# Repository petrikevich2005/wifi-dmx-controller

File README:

этот репозиторий предназначен для хранения прошивки микроконтроллера этого проекта: https://docs.google.com/document/d/1X2l_9bCAOKjv8QiKN7pxREiMzuwiFvaY4nnqX09m9t8/edit?usp=sharing

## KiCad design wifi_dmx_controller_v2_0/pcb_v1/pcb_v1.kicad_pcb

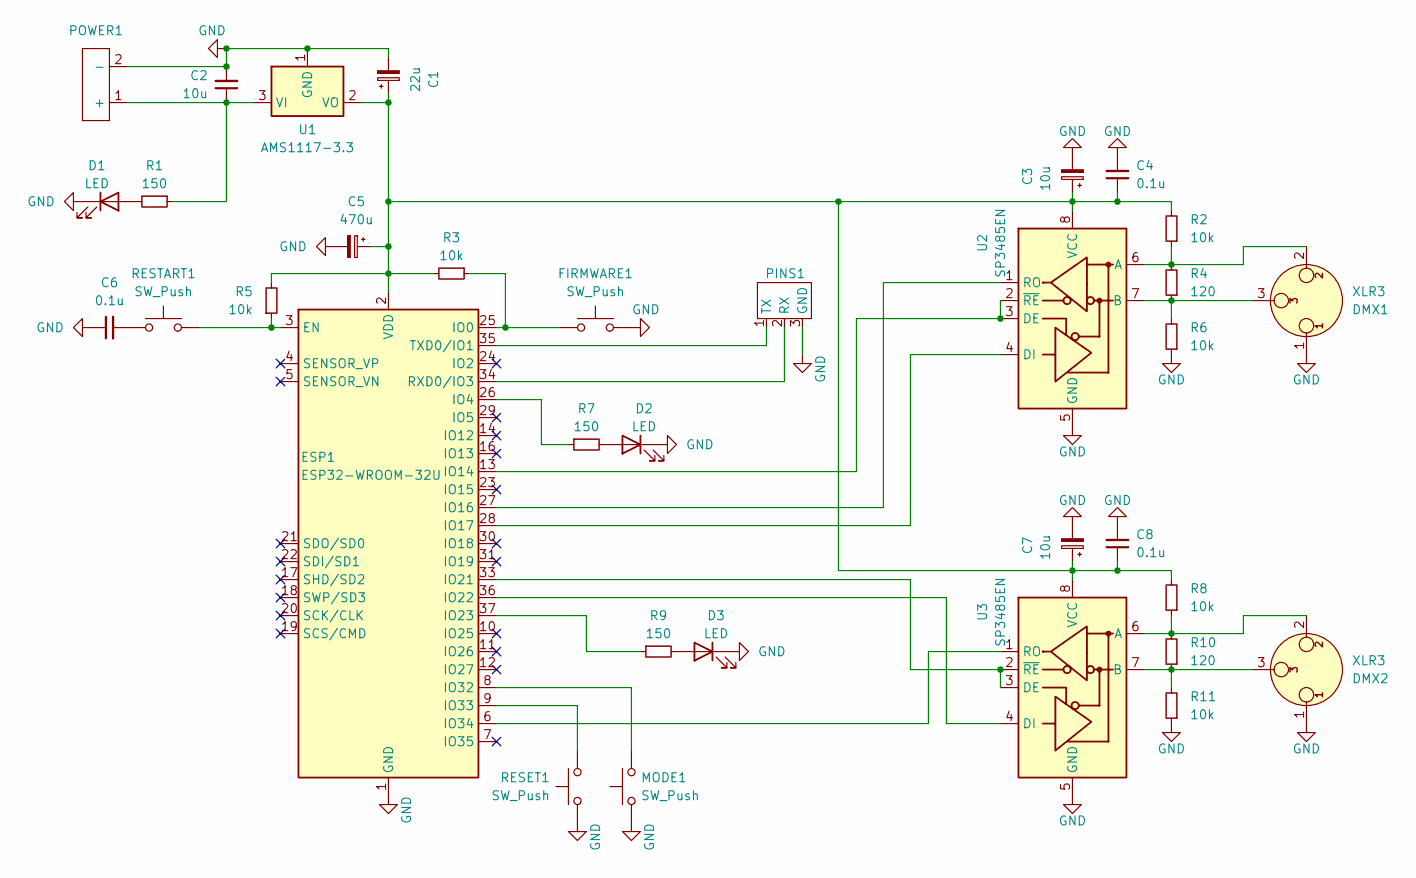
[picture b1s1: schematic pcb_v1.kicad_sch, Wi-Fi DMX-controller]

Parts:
C1: 22u; CP_Radial_D6.3mm_P2.50mm
C2: 10u; C_0805_2012Metric
C3, C7: 10u; CP_Radial_D4.0mm_P2.00mm
C4, C6, C8: 0.1u; C_1206_3216Metric
C5: 470u; CP_Radial_D6.3mm_P2.50mm
D1, D2, D3: LED; LED_D5.0mm_Clear
DMX1, DMX2: XLR3; 3pin_3-1.5mm
ESP1: ESP32-WROOM-32U
FIRMWARE1: SW_Push; 2pin_2-1-2.54mm
MODE1: SW_Push; 2pin_2-1-2.54mm
PINS1: tx_rx_gnd
POWER1: 5V; 2pin_2-1mm
R1, R7, R9: 150; R_1206_3216Metric
R2, R3, R5, R6, R8, R11: 10k; R_0805_2012Metric
R4, R10: 120; R_1206_3216Metric
RESET1: SW_Push; 2pin_2-1-2.54mm
RESTART1: SW_Push; 2pin_2-1-2.54mm
U1: AMS1117-3.3; SOT-223-3_TabPin2
U2, U3: SP3485EN; SOIC-8_3.9x4.9mm_P1.27mm

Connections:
GND: C1.2, C2.2, C3.2, C4.2, C5.2, C6.1, C7.2, C8.2, D1.1 (K), D2.1 (K), D3.1 (K), DMX1.1, DMX2.1, ESP1.1 (GND), ESP1.15 (GND), ESP1.38 (GND), ESP1.39 (GND), FIRMWARE1.2, MODE1.1, PINS1.3 (GND), POWER1.2 (-), R6.1, R11.1, RESET1.2, U1.1 (GND), U2.5 (GND), U3.5 (GND)
unnamed: C6.2, RESTART1.1
unnamed: D1.2 (A), R1.2
unnamed: D2.2 (A), R7.2
unnamed: D3.2 (A), R9.2
unnamed: ESP1.3 (EN), R5.1, RESTART1.2
unnamed: ESP1.25 (IO0), FIRMWARE1.1, R3.1
unnamed: ESP1.26 (IO4), R7.1
unnamed: ESP1.13 (IO14), U2.2 (~RE), U2.3 (DE)
unnamed: ESP1.27 (IO16), U2.1 (RO)
unnamed: ESP1.28 (IO17), U2.4 (DI)
unnamed: ESP1.33 (IO21), U3.2 (~RE), U3.3 (DE)
unnamed: ESP1.36 (IO22), U3.4 (DI)
unnamed: ESP1.37 (IO23), R9.1
unnamed: ESP1.8 (IO32), MODE1.2
unnamed: ESP1.9 (IO33), RESET1.1
unnamed: ESP1.6 (IO34), U3.1 (RO)
unnamed: ESP1.34 (RXD0/IO3), PINS1.2 (RX)
unnamed: ESP1.35 (TXD0/IO1), PINS1.1 (TX)
unnamed: C1.1, C3.1, C4.1, C5.1, C7.1, C8.1, ESP1.2 (VDD), R2.2, R3.2, R5.2, R8.2, U1.2 (VO), U2.8 (VCC), U3.8 (VCC)
unnamed: C2.1, POWER1.1 (+), R1.1, U1.3 (VI)
unnamed: DMX1.2, R2.1, R4.2, U2.6 (A)
unnamed: DMX1.3, R4.1, R6.2, U2.7 (B)
unnamed: DMX2.2, R8.1, R10.2, U3.6 (A)
unnamed: DMX2.3, R10.1, R11.2, U3.7 (B)

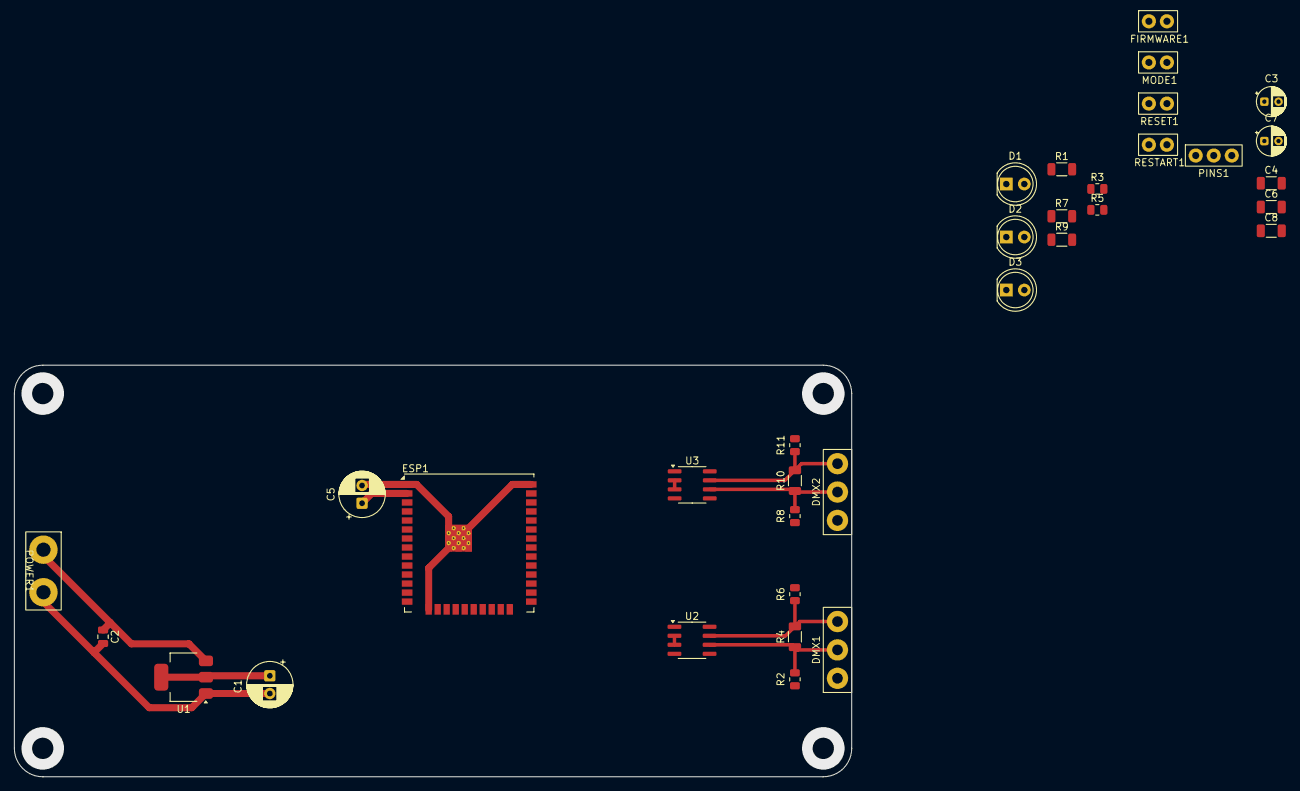
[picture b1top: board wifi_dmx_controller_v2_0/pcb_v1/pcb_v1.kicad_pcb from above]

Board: 2 copper layers, 118.0 x 58.0 mm, 34 parts (0 on the bottom side), 25 nets.

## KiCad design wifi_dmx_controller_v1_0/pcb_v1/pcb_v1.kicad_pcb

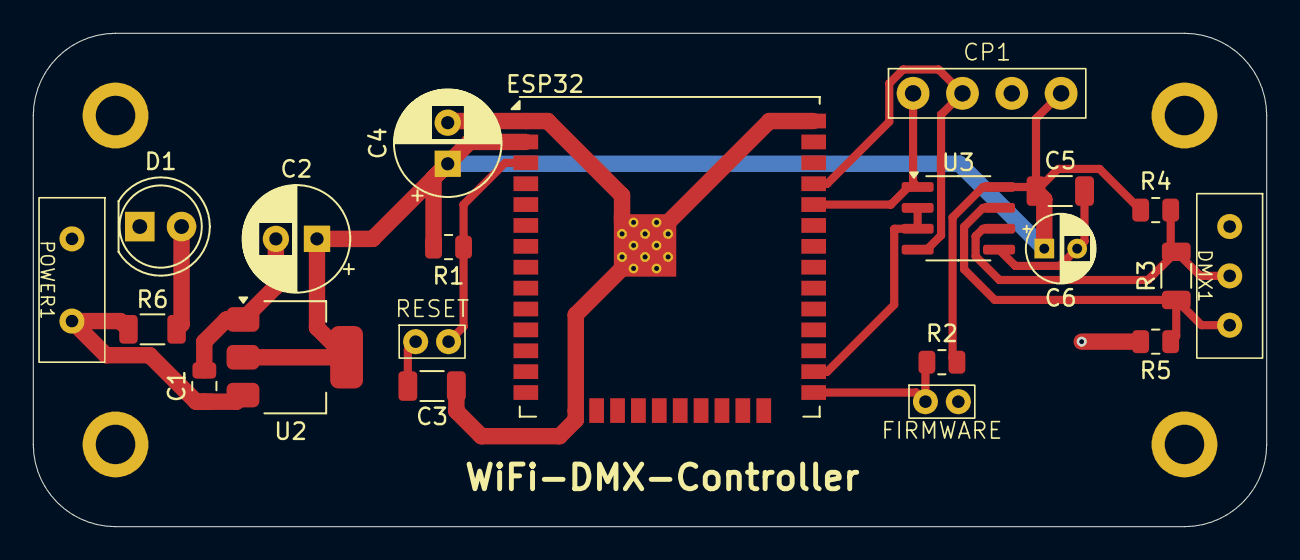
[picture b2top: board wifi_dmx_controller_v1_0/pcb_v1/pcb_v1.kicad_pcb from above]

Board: 2 copper layers, 75.0 x 30.0 mm, 21 parts (0 on the bottom side), 12 nets.

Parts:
C1: 10u; C_0805_2012Metric
C2: 22u; CP_Radial_D6.3mm_P2.50mm
C3, C5: 0.1u; C_1206_3216Metric
C4: 470u; CP_Radial_D6.3mm_P2.50mm
C6: 10u; CP_Radial_D4.0mm_P2.00mm
CP1: CP2102; CP2102_Conn
D1: LED; LED_D5.0mm_Clear
DMX1: XLR3; 3pin_10mm
ESP32: ESP32-WROOM-32U
FIRMWARE: SW_Push; small_2pin
POWER1: 5V; 2pin_10mm
R1, R2, R4, R5: 10k; R_0805_2012Metric
R3: 120; R_1206_3216Metric
R6: 150; R_1206_3216Metric
RESET: SW_Push; small_2pin
U2: AMS1117-3.3; SOT-223-3_TabPin2
U3: SP3485EN; SOIC-8_3.9x4.9mm_P1.27mm

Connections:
GND: C1.2, C2.2, C3.1, C4.2, C5.2, C6.2, CP1.3 (GND), D1.1 (K), DMX1.1, ESP32.1 (GND), ESP32.15 (GND), ESP32.38 (GND), ESP32.39 (GND), FIRMWARE.2, POWER1.1, R5.1, U2.1 (GND), U3.5 (GND)
unnamed: C3.2, RESET.1
unnamed: C2.1, C4.1, C5.1, C6.1, CP1.4 (3V3), ESP32.2 (VDD), R1.1, R2.2, R4.2, U2.2 (VO), U3.8 (VCC)
unnamed: CP1.1 (RXD), ESP32.34 (RXD0/IO3), U3.1 (RO)
unnamed: CP1.2 (TXD), ESP32.35 (TXD0/IO1), U3.4 (DI)
unnamed: D1.2 (A), R6.2
unnamed: ESP32.3 (EN), R1.2, RESET.2
unnamed: ESP32.25 (IO0), FIRMWARE.1, R2.1
unnamed: ESP32.26 (IO4), U3.2 (~RE), U3.3 (DE)
unnamed: C1.1, POWER1.2, R6.1, U2.3 (VI)
unnamed: DMX1.2, R3.2, R4.1, U3.6 (A)
unnamed: DMX1.3, R3.1, R5.2, U3.7 (B)

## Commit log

2025-02-22 gpt review
2025-02-22 cpp to ino format
2025-03-07 make pcb
2025-03-11 all pcb remake
2025-03-24 pcb update (for box G1068B)
2025-06-21 worked code
2025-06-21 stable 22 june 2025
2025-06-23 stable v1.0
2025-07-21 update and create light_baza
2025-10-01 code from freedom (baza)
2025-10-01 main fix (check with Artem; did it the way it was on the base)
2025-10-04 main sketch with web-interfaice be created (not testing artnet/dmx)
2025-10-16 structur update
2025-10-16 start creation version 2
2025-10-16 lite version sketch (only ap and artnet)
2025-10-16 start creation ZakVersion sketch
2025-10-20 it work, but web server load 300 ms..
2025-10-21 link web to reset button (recovery_mode)
2025-10-22 start new direction
2025-10-23 make static ip
